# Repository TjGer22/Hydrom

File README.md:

# Hydrom Firmware

This directory contains the ESP32 firmware for the Hydrom smart hydrometer, built with [PlatformIO](https://platformio.org/) on the Arduino framework.

## Target Hardware

**Heltec WiFi LoRa 32 V2** — ESP32 with integrated OLED and LoRa (only the ESP32 core is used; LoRa is not used in this project).

## Directory Structure

```
firmware/
├── src/              # main.cpp — application entry point
├── lib/              # Project-specific libraries
│   ├── ArduAutoUpdater/   # OTA firmware update
│   ├── BTManager/         # Bluetooth LE (BLE iBeacon)
│   ├── Calibrator/        # Gravity calibration logic
│   ├── DeviceManager/     # Device lifecycle management
│   ├── FileManager/       # SPIFFS configuration storage
│   ├── FindCurve/         # Polynomial curve fitting
│   ├── I2Cdevlib-Core/    # I2C abstraction (vendored)
│   ├── I2Cdevlib-MPU6050/ # MPU6050 IMU driver (vendored)
│   ├── NetworkManager/    # Wi-Fi (AP + client mode)
│   ├── SensorManager/     # IMU + DS18B20 sensor handling
│   ├── ServiceManager/    # Cloud service integrations
│   ├── Utils/             # Shared utilities
│   └── WebManager/        # Embedded Web UI
├── data/             # SPIFFS assets (logo, font, favicon)
├── Flasher/          # Helper scripts for manual flashing
├── platformio.ini    # Build configuration
└── partitions_custom8MB.csv  # Custom 8 MB partition table
```

## Installing the Firmware (no development tools required)

The installer scripts download the latest release from GitHub and flash it
to your Hydrom automatically. You only need an internet connection and a USB
cable that supports data transfer.

### Windows

Open **PowerShell** (search for it in the Start menu) and paste:

```powershell
powershell -ExecutionPolicy Bypass -Command "irm https://raw.githubusercontent.com/TjGer22/Hydrom/main/firmware/Flasher/install.ps1 | iex"
```

The script will:

1. Install Python 3 if it is not already present (via winget or direct download)
2. Install esptool via pip
3. Detect the COM port of your Hydrom automatically
4. Download the latest firmware files from the GitHub Releases page
5. Flash all five binary files in the correct order

> **Driver note** — if no COM port is detected, install the CP2102 driver first:
> https://www.silabs.com/developers/usb-to-uart-bridge-vcp-drivers

---

### macOS

Open **Terminal** and paste:

```bash
curl -fsSL https://raw.githubusercontent.com/TjGer22/Hydrom/main/firmware/Flasher/install.sh | bash
```

---

### Linux

```bash
curl -fsSL https://raw.githubusercontent.com/TjGer22/Hydrom/main/firmware/Flasher/install.sh | bash
```

> **Permission note** — if the flash fails with a permission error, add your user
> to the `dialout` group, then log out and back in:
> ```bash
> sudo usermod -aG dialout $USER
> ```

---

### Overriding port or baud rate

If the installer cannot find the device automatically, you can pass the port
and baud rate as environment variables before the command:

**macOS / Linux:**
```bash
HYDROM_PORT=/dev/ttyUSB0 HYDROM_BAUD=115200 \
  curl -fsSL https://raw.githubusercontent.com/TjGer22/Hydrom/main/firmware/Flasher/install.sh | bash
```

**Windows (PowerShell):**
```powershell
$env:HYDROM_PORT="COM3"; $env:HYDROM_BAUD="115200"
powershell -ExecutionPolicy Bypass -Command "irm https://raw.githubusercontent.com/TjGer22/Hydrom/main/firmware/Flasher/install.ps1 | iex"
```

---

### What happens during flashing

The installer writes five binary files to specific addresses in the ESP32 flash:

| File | Address | Purpose |
|------|---------|---------|
| `bootloader_dio_40m.bin` | `0x1000` | ESP32 first-stage bootloader |
| `partitions.bin` | `0x8000` | Partition table (8 MB layout) |
| `boot_app0.bin` | `0xe000` | OTA selection bootloader |
| `firmware.bin` | `0x10000` | Application firmware |
| `spiffs.bin` | `0x5B0000` | Filesystem (Web UI assets) |

When prompted, hold the **BOOT** button on the Hydrom and release it once
you see `Connecting...` in the output.

---

## Building from Source (PlatformIO)

```bash
# Build firmware + SPIFFS image
pio run --environment local --target buildfs
pio run --environment local

# Flash to connected device
pio run --environment local --target upload
pio run --environment local --target uploadfs

# Open serial monitor
pio device monitor
```

## Building

```bash
# Build firmware + SPIFFS image
pio run --environment local --target buildfs
pio run --environment local

# Flash to connected device
pio run --environment local --target upload
pio run --environment local --target uploadfs

# Open serial monitor
pio device monitor
```

## Credentials

Copy `lib/FileManager/Credentials.txt.example` to `lib/FileManager/Credentials.txt` and fill in your own values.
The `Credentials.txt` file is listed in `.gitignore` and will **never** be committed.

## License

GPL v3 — see [../LICENSE](../LICENSE)

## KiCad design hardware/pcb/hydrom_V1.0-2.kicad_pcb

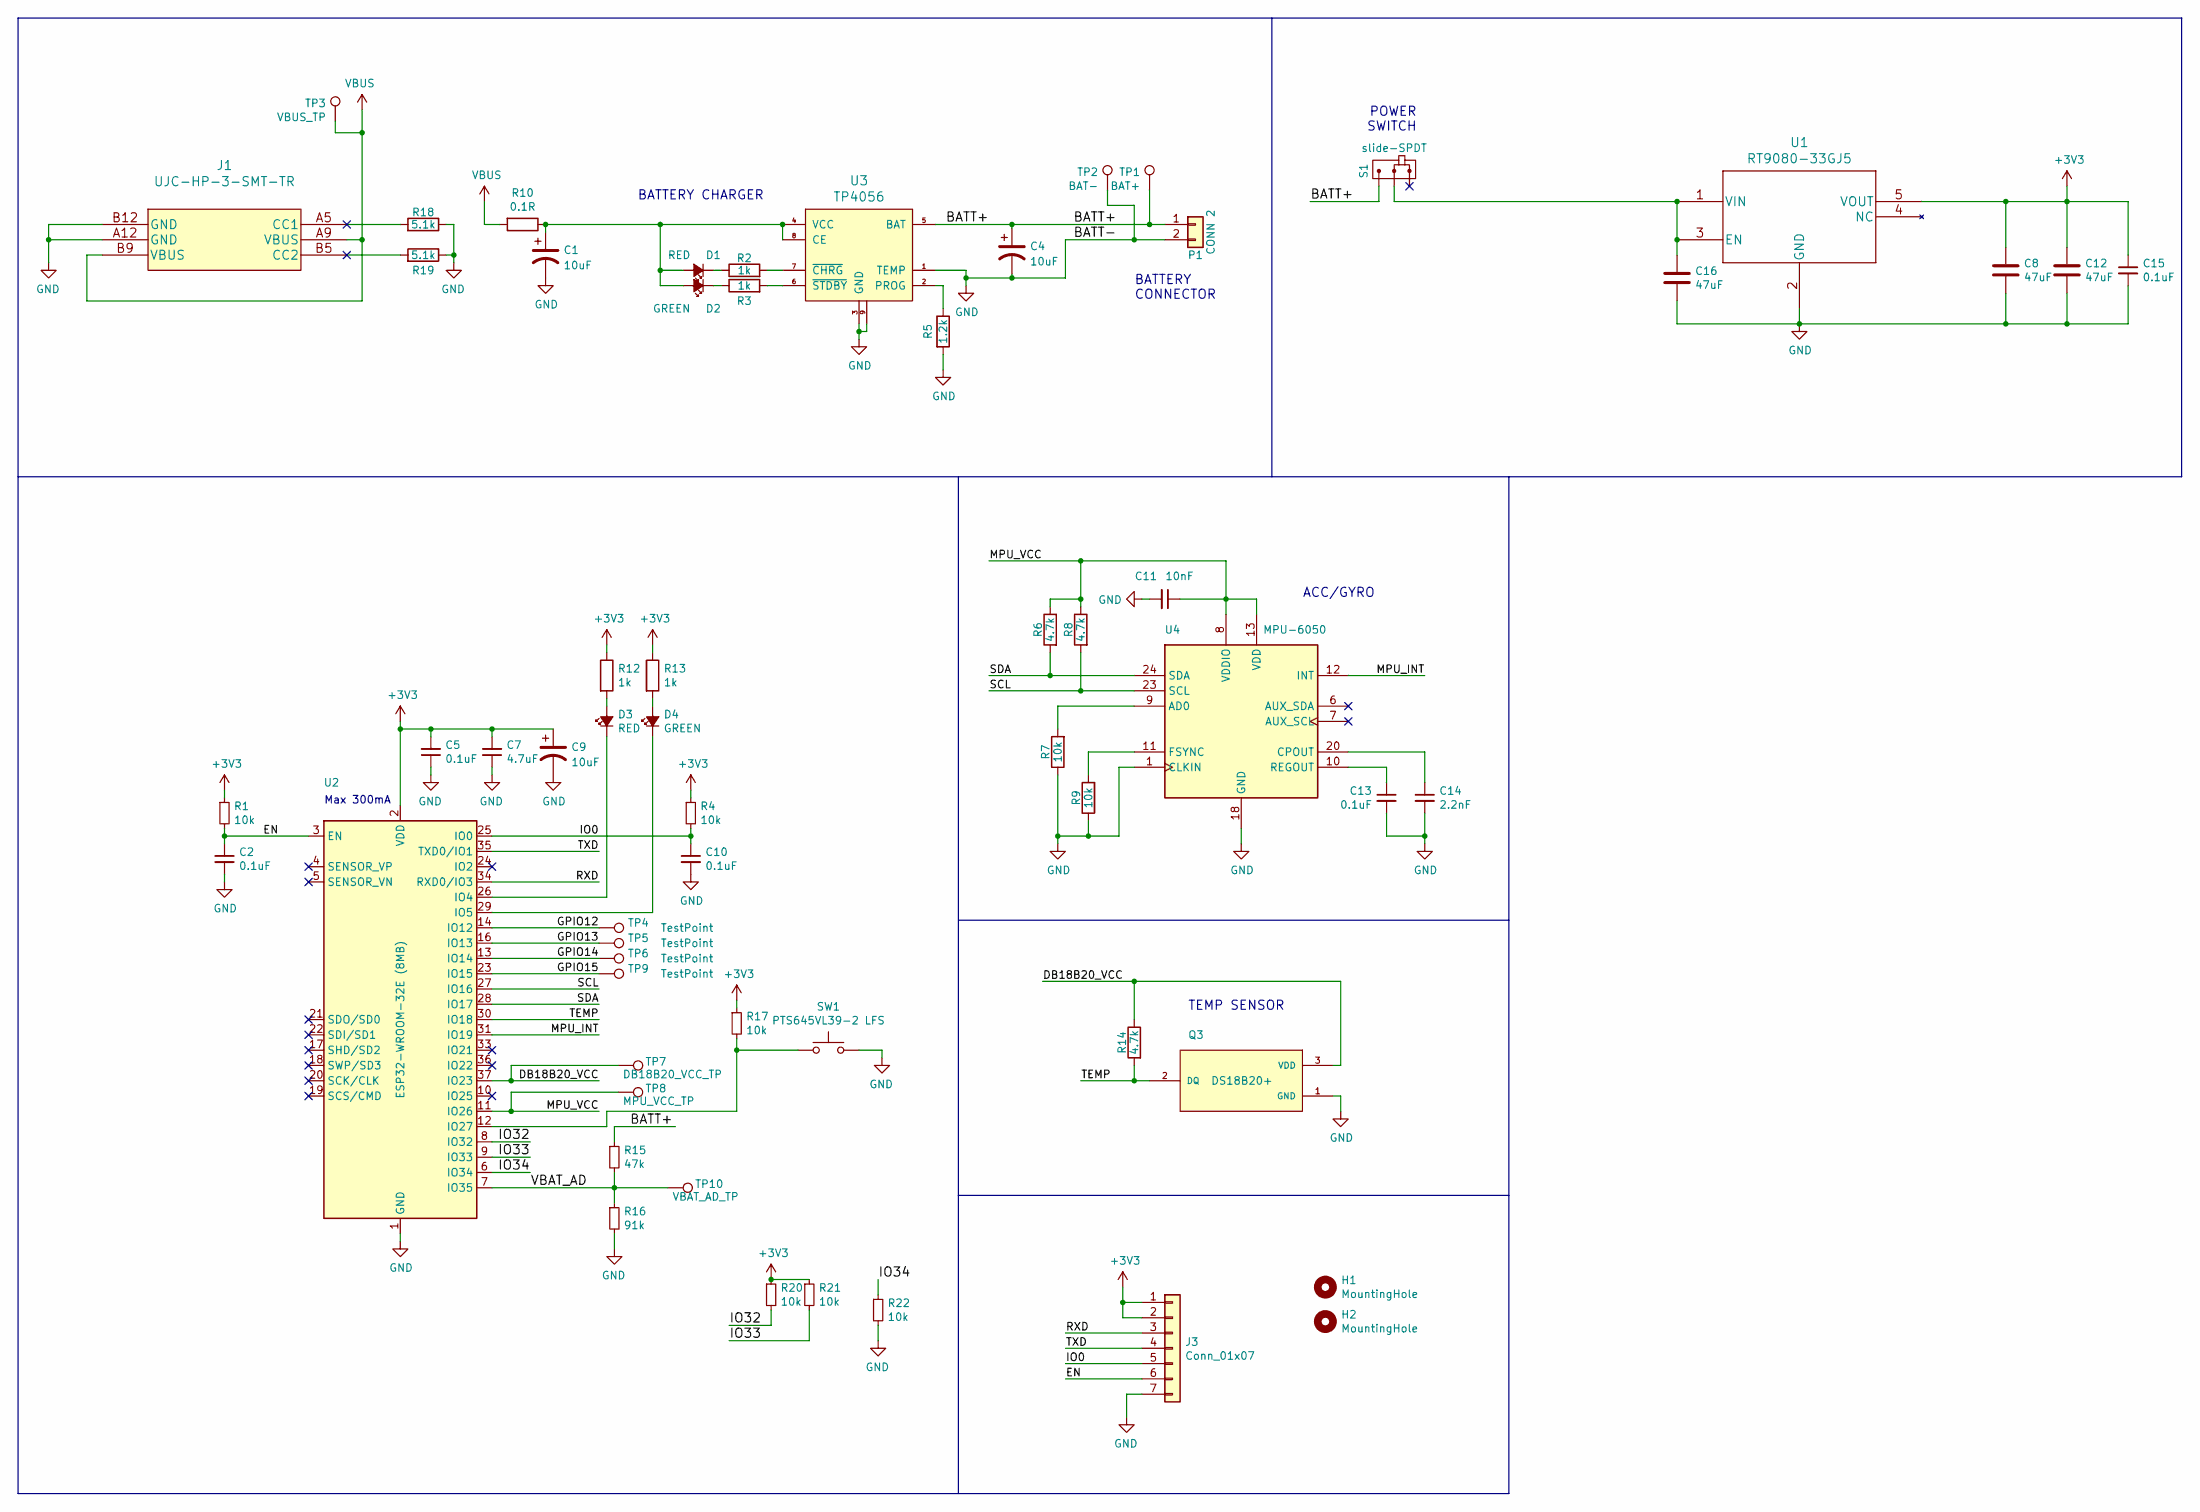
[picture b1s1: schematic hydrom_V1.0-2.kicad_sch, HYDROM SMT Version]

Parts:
C1, C4, C9: 10uF; CP_EIA-3216-18_Kemet-A; MPN 293D106X0010A2TE3; LCSC.com PN C2156473
C2, C5, C10, C13, C15: 0.1uF; C_0603_1608Metric; MPN CL10B104KB8WPNC; Digi-Key_PN 1276-1000-1-ND
C7: 4.7uF; C_0603_1608Metric; MPN CL10A475KP8NNNC; Digi-Key_PN 1276-2087-1-ND
C8, C12, C16: 47uF; C_0603_1608Metric; MPN C1206B476M016T; LCSC.com PN C607993
C11: 10nF; C_0603_1608Metric; MPN CL10B103KB8NNNL; Digi-Key_PN 445-1311-1-ND
C14: 2.2nF; C_0603_1608Metric; MPN CL10B222KB8NNNC; Digi-Key_PN 399-1085-1-ND
D1, D3: RED; LED_0805_2012Metric; MPN 150080RS75000; Digi-Key_PN 160-1427-1-ND
D2, D4: GREEN; LED_0805_2012Metric; MPN 150080GS75000; Digi-Key_PN 160-1423-1-ND
H1, H2: MountingHole; MountingHole_3.2mm_M3; MPN Does not apply; LCSC.com PN Does not apply
J1: UJC-HP-3-SMT-TR; 217175-0001; MPN UJC-HP-3-SMT-TR; Mouser PN 490-UJC-HP-3-SMT-TR
J3: Conn_01x07; PinHeader_1x07_P2.54mm_Vertical
P1: CONN 2; New_BAT_HOL
Q3: DS18B20+; TO-92_Inline_Wide; MPN DS18B20+T&R; Digi-Key_PN DS18B20+T&RCT-ND
R1, R4, R7, R9, R17, R20, R21, R22: 10k; R_0603_1608Metric; MPN SFR03EZPF1002; Digi-Key_PN 311-10.0KHRCT-ND
R2, R3, R12, R13: 1k; R_0603_1608Metric; MPN ESR03EZPF1001; Digi-Key_PN MCT0603-1.00K-CFCT-ND
R5: 1.2k; R_0603_1608Metric; MPN WR06X1201FTL; Digi-Key_PN MCT0603-1.20K-CFCT-ND
R6, R8, R14: 4.7k; R_0603_1608Metric; MPN RC0603FR-074K7L; Digi-Key_PN 311-4.70KHRCT-ND
R10: 0.1R; R_0603_1608Metric; MPN UCR03EVPFLR100; LCSC.com PN C880952
R15: 47k; R_0603_1608Metric; MPN AC0603FR-0747KL; Digi-Key_PN 311-10.0KHRCT-ND
R16: 91k; R_0603_1608Metric; MPN RC0603FR-0790K9L; Digi-Key_PN 311-10.0KHRCT-ND
R18, R19: 5.1k; R_0603_1608Metric; MPN RC0603FR-075K1L; Digi-Key_PN MCT0603-1.00K-CFCT-ND
S1: slide-SPDT; Slide_Switch; MPN SK12D07VG4NSPA; Mouser PN 611-SK12D07VG4NSPA
SW1: PTS645VL39-2 LFS; SW_Tactile_SPST_Angled_PTS645Vx39-2LFS; MPN PTS645VL39-2 LFS; Digi-Key_PN CKN9103-ND
TP1: BAT+; TestPoint_Loop_D1.80mm_Drill1.0mm_Beaded; MPN Does not apply; LCSC.com PN Does not apply
TP2: BAT-; TestPoint_Loop_D1.80mm_Drill1.0mm_Beaded; MPN Does not apply; LCSC.com PN Does not apply
TP3: VBUS_TP; TestPoint_Loop_D1.80mm_Drill1.0mm_Beaded; MPN Does not apply; LCSC.com PN Does not apply
TP4, TP5, TP6, TP9: TestPoint; TestPoint_Loop_D1.80mm_Drill1.0mm_Beaded; MPN Does not apply; LCSC.com PN Does not apply
TP7: DB18B20_VCC_TP; TestPoint_Loop_D1.80mm_Drill1.0mm_Beaded; MPN Does not apply; LCSC.com PN Does not apply
TP8: MPU_VCC_TP; TestPoint_Loop_D1.80mm_Drill1.0mm_Beaded; MPN Does not apply; LCSC.com PN Does not apply
TP10: VBAT_AD_TP; TestPoint_Loop_D1.80mm_Drill1.0mm_Beaded; MPN Does not apply; LCSC.com PN Does not apply
U1: RT9080-33GJ5; SOT-23-5; MPN TPRT9080-33GJ5; LCSC.com PN C2959864
U2: ESP32-WROOM-32E (8MB); ESP32-WROOM-32; MPN ESP32-WROOM-32E(M113EH2800PH3Q0); Digi-Key_PN 1965-ESP32-WROOM-32E(8MB)CT-ND
U3: TP4056; SOIC127P600X175-9N; MPN TP4056; LCSC.com PN C382139
U4: MPU-6050; InvenSense_QFN-24_4x4mm_P0.5mm; MPN MPU-6050; Digi-Key_PN 1428-1007-1-ND

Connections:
+3V3: C5.2, C7.2, C8.1, C9.1, C12.1, C15.1, J3.1, J3.2, R1.1, R4.1, R12.1, R13.1, R17.1, R20.1, R21.1, U1.5 (VOUT), U2.2 (VDD)
/BATT+: C4.1, P1.1, R15.1, S1.A, TP1.1, U3.5 (BAT)
/DB18B20_VCC: Q3.3 (VDD), R14.1, TP7.1, U2.37 (IO23)
/EN: C2.1, J3.6, R1.2, U2.3 (EN)
/GPIO12: TP4.1, U2.14 (IO12)
/GPIO13: TP5.1, U2.16 (IO13)
/GPIO14: TP6.1, U2.13 (IO14)
/GPIO15: TP9.1, U2.23 (IO15)
/IO0: C10.1, J3.5, R4.2, U2.25 (IO0)
/IO32: R20.2, U2.8 (IO32)
/IO33: R21.2, U2.9 (IO33)
/IO34: R22.1, U2.6 (IO34)
/MPU_INT: U2.31 (IO19), U4.12 (INT)
/MPU_VCC: C11.1, R6.1, R8.1, TP8.1, U2.11 (IO26), U4.8 (VDDIO), U4.13 (VDD)
/RXD: J3.3, U2.34 (RXD0/IO3)
/SCL: R8.2, U2.27 (IO16), U4.23 (SCL)
/SDA: R6.2, U2.28 (IO17), U4.24 (SDA)
/TEMP: Q3.2 (DQ), R14.2, U2.30 (IO18)
/TXD: J3.4, U2.35 (TXD0/IO1)
/VBAT_AD: R15.2, R16.1, TP10.1, U2.7 (IO35)
GND: C1.2, C2.2, C4.2, C5.1, C7.1, C8.2, C9.2, C10.2, C11.2, C12.2, C13.2, C14.2, C15.2, C16.2, J1.A12 (GND), J1.B12 (GND), J3.7, P1.2, Q3.1 (GND), R5.2, R7.1, R9.1, R16.2, R18.1, R19.1, R22.2, SW1.2, TP2.1, U1.2 (GND), U2.1 (GND), U2.15 (GND), U2.38 (GND), U2.39 (GND), U3.1 (TEMP), U3.3 (GND), U3.9, U4.1 (CLKIN), U4.18 (GND)
unnamed: C1.1, D1.2 (A), D2.2 (A), R10.1, U3.4 (VCC), U3.8 (CE)
unnamed: C13.1, U4.10 (REGOUT)
unnamed: C14.1, U4.20 (CPOUT)
unnamed: C16.1, S1.COM, U1.1 (VIN), U1.3 (EN)
unnamed: D1.1 (K), R2.1
unnamed: D2.1 (K), R3.1
unnamed: D3.1 (K), U2.26 (IO4)
unnamed: D3.2 (A), R12.2
unnamed: D4.1 (K), U2.29 (IO5)
unnamed: D4.2 (A), R13.2
unnamed: R2.2, U3.7 (~CHRG)
unnamed: R3.2, U3.6 (~STDBY)
unnamed: R5.1, U3.2 (PROG)
unnamed: R7.2, U4.9 (AD0)
unnamed: R9.2, U4.11 (FSYNC)
unnamed: R17.2, SW1.1, U2.12 (IO27)
VBUS: J1.A9 (VBUS), J1.B9 (VBUS), R10.2, TP3.1

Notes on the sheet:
BATTERY CONNECTOR
Max 300mA
POWER SWITCH
ACC/GYRO
TEMP SENSOR
BATTERY CHARGER

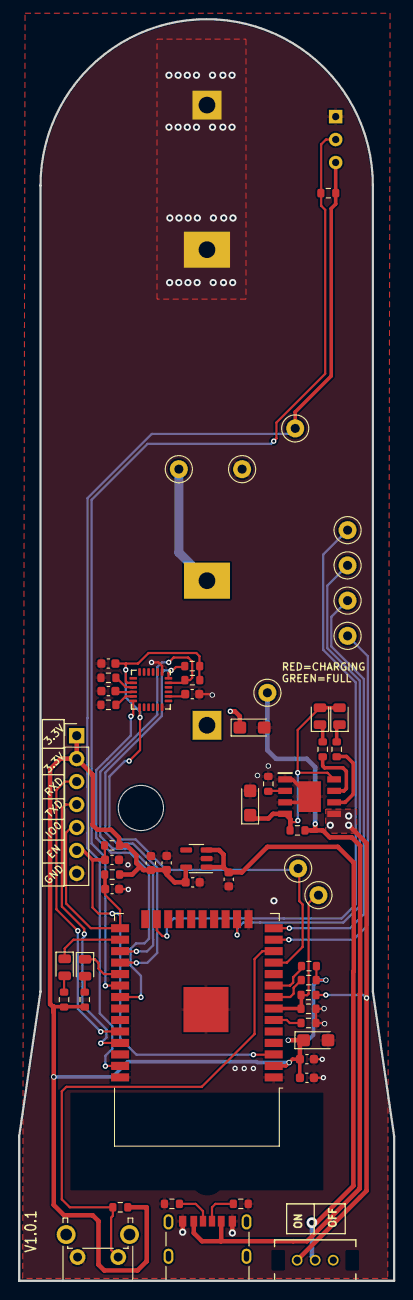
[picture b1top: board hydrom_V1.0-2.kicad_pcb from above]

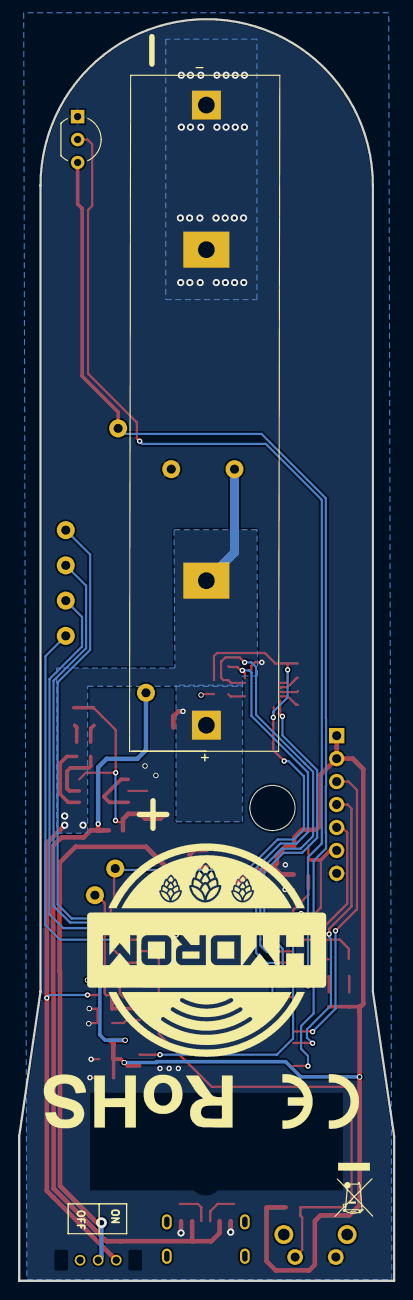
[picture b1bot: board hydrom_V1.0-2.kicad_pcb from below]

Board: 2 copper layers, 41.5 x 139.6 mm, 60 parts (2 on the bottom side), 38 nets.

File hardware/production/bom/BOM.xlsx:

Reference(s) | Qty | Value | Footprint | Mfr# | Manufacturer | Supplier
C1, C4, C9 | 3 | 10uF | Capacitor_Tantalum_SMD:CP_EIA-3216-18_Kemet-A | CA45-A010K106T | Hunan Xiangyee in S&T | LCSC
C2, C5, C10, C13, C15 | 5 | 0.1uF | Capacitor_SMD:C_0603_1608Metric | CC0603KRX7R9BB104 | Yageo | LCSC
C7 | 1 | 4.7uF | Capacitor_SMD:C_0603_1608Metric | CL10A475KQ8NNNC | Samsung Electro-Mechanics | LCSC
C8, C12, C16 | 3 | 47uF | Capacitor_SMD:C_1206_3216Metric | GRM188R60J476ME15D | Murata Electronics | LCSC
C11 | 1 | 10nF | Capacitor_SMD:C_0603_1608Metric | CC0603KRX7R9BB103 | Yageo | LCSC
C14 | 1 | 2.2nF | Capacitor_SMD:C_0603_1608Metric | 603B222K250NT | FH(Guangdong Fenghua Advanced Tech) | LCSC
D1, D3 | 2 | RED | LED_SMD:LED_0805_2012Metric | XL-2012SURC | XINGLIGHT | LCSC
D2, D4 | 2 | GREEN | LED_SMD:LED_0805_2012Metric | XL-2012SYGC | XINGLIGHT | LCSC
J1 | 1 | UJC-HP-3-SMT-TR | footprints:217175-0001 | UJC-HP-3-SMT-TR | CUI Devices | Mouser
P1 | 2 | CONN 2 | greencharge-footprints:MY-18650-02 | MY-18650-02 | MYOUNG | LCSC
Q3 | 1 | DS18B20+ | Package_TO_SOT_THT:TO-92_Inline_Wide | DS18B20+ | Maxim Integrated | LCSC
R1, R4, R7, R9, R17, R20, R21, R22 | 8 | 10k | Resistor_SMD:R_0603_1608Metric | 0603WAF1002T5E | UNI-ROYAL(Uniroyal Elec) | LCSC
R2, R3, R12, R13 | 4 | 1k | Resistor_SMD:R_0603_1608Metric | 0603WAF1001T5E | UNI-ROYAL(Uniroyal Elec) | LCSC
R5 | 1 | 1.2k | Resistor_SMD:R_0603_1608Metric | 0603WAF1201T5E | UNI-ROYAL(Uniroyal Elec) | LCSC
R6, R8, R14 | 3 | 4.7k | Resistor_SMD:R_0603_1608Metric | FRC0603J472 TS | FOJAN | LCSC
R10 | 1 | 0.1R | Resistor_SMD:R_0603_1608Metric | FRL0603JR100TS | FOJAN | LCSC
R15 | 1 | 47k | Resistor_SMD:R_0603_1608Metric | FRC0603J473 TS | FOJAN | LCSC
R16 | 1 | 91k | Resistor_SMD:R_0603_1608Metric | FRC0603J913 TS | FOJAN | LCSC
R18, R19 | 2 | 5.1k | Resistor_SMD:R_0603_1608Metric | FRC0603J512 TS | FOJAN | LCSC
S1 | 1 | slide-SPDT | iSpindel:Slide_Switch | SK12D07VG4NSPA | C&K | Mouser
SW1 | 1 | PTS645VL39-2 LFS | Button_Switch_THT:SW_Tactile_SPST_Angled_PTS645Vx39-2LFS | PTS645VL392LFS | C&K | LCSC
U1 | 1 | RT9080-33GJ5 | Package_TO_SOT_SMD:SOT-23-5 | TPRT9080-33GJ5 | TECH PUBLIC | LCSC
U2 | 1 | ESP32-WROOM-32E (8MB) | RF_Module:ESP32-WROOM-32 | ESP32-WROOM-32-N4 | Espressif Systems | LCSC
U3 | 1 | TP4056 | SamacSys_Parts:SOIC127P600X175-9N | TP4056 | UMW(Youtai Semiconductor Co., Ltd.) | LCSC
U4 | 1 | MPU-6050 | Sensor_Motion:InvenSense_QFN-24_4x4mm_P0.5mm | MPU-6050 | TDK InvenSense | LCSC
 |  |  |  |  |  | LCSC

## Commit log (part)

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2026-03-09 Create LICENSE
2026-03-09 Update README.md (#1)

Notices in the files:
parts and their libraries:
Copyright 2021 Accelerated Designs. All rights reserved.
